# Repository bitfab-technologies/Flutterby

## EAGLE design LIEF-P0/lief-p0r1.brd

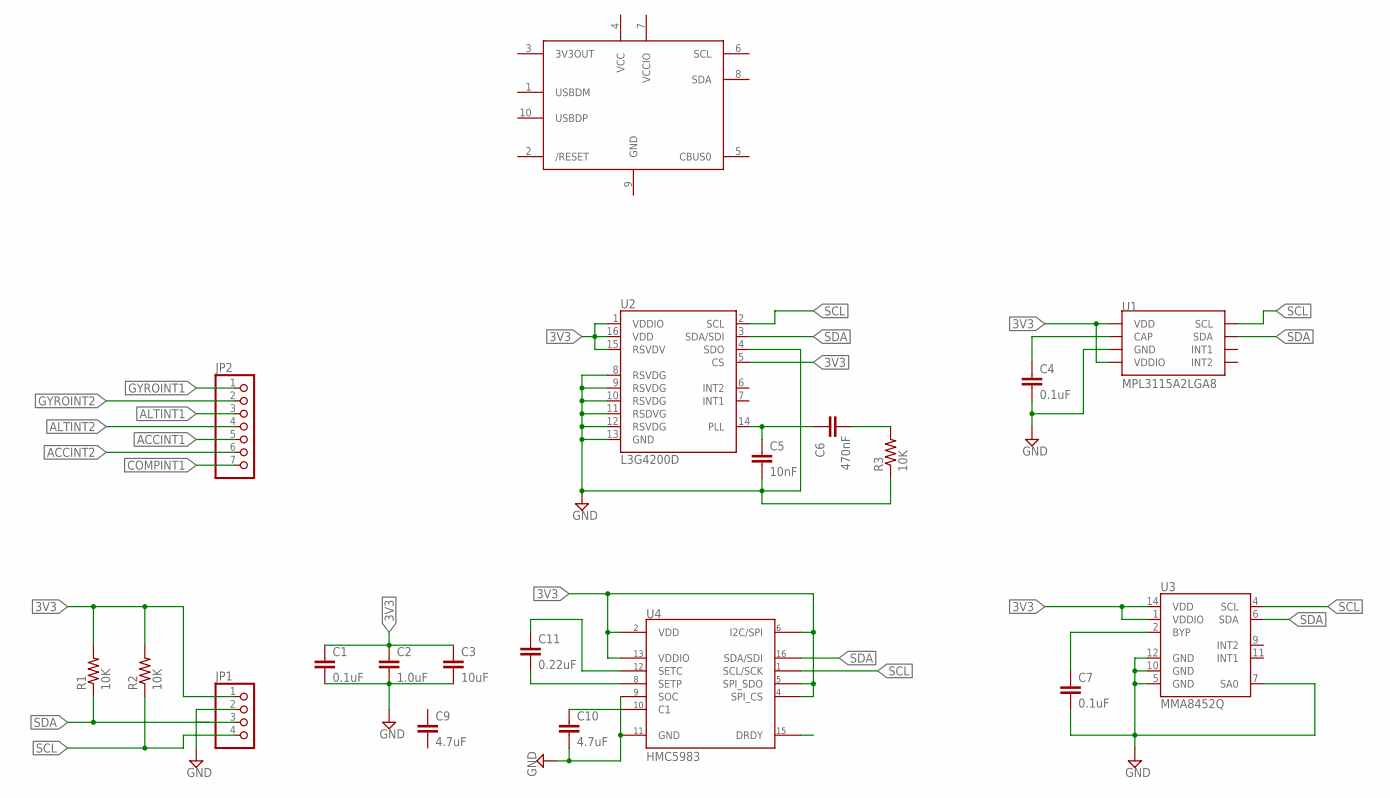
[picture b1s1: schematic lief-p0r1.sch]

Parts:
C1, C7: 0.1uF; 0603-CAP
C2: 1.0uF; 0805-CAP
C3: 10uF; 0805-CAP
C4: 0.1uF; 0805-CAP
C5: 10nF; 0805-CAP
C6: 470nF; 0805-CAP
C9: 4.7uF; 0603-CAP
C10: 4.7uF; 0805-CAP
C11: 0.22uF; 0805-CAP
JP1: PINHD-1X4; 1X04
JP2: PINHD-1X7; 1X07
R1, R2, R3: 10K; 0204V
U1: MPL3115A2LGA8; LGA8
U2: L3G4200D; LGA16-4X4
U3: MMA8452Q; QFN-16_0.5MM
U4: HMC5983; HMC5983-LPCC16
U$1: FT200XD; DFN-10

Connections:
3V3: C1.1, C2.1, C3.1, JP1.1, R1.2, R2.2, U1.1 (VDD), U1.4 (VDDIO), U2.1 (VDDIO), U2.5 (CS), U2.15 (RSVDV), U2.16 (VDD), U3.1 (VDDIO), U3.14 (VDD), U4.I2C/SPI, U4.SPI_CS/S1 (SPI_CS), U4.SPI_SDO, U4.VDD, U4.VDDIO
ACCINT1: JP2.5
ACCINT2: JP2.6
ALTINT1: JP2.3
ALTINT2: JP2.4
COMPINT1: JP2.7
GND: C1.2, C2.2, C3.2, C4.2, C5.2, C7.2, C10.2, JP1.2, JP1.3, R3.1, U1.3 (GND), U2.4 (SDO), U2.8 (RSVDG), U2.9 (RSVDG), U2.10 (RSVDG), U2.11 (RSDVG), U2.12 (RSVDG), U2.13 (GND), U3.5 (GND), U3.7 (SA0), U3.10 (GND), U3.12 (GND), U4.GND, U4.SOC
GYROINT1: JP2.1
GYROINT2: JP2.2
unnamed: C11.1, U4.SETC
unnamed: C4.1, U1.2 (CAP)
unnamed: C6.2, R3.2
unnamed: C5.1, C6.1, U2.14 (PLL)
unnamed: C7.1, U3.2 (BYP)
unnamed: C11.2, U4.SETP
unnamed: C10.1, U4.C1
SCL: JP1.4, R2.1, U1.8 (SCL), U2.2 (SCL), U3.4 (SCL), U4.SCL/SPI_SCK (SCL/SCK)
SDA: R1.1, U1.7 (SDA), U2.3 (SDA/SDI), U3.6 (SDA), U4.SDA/SPI_SDI (SDA/SDI)

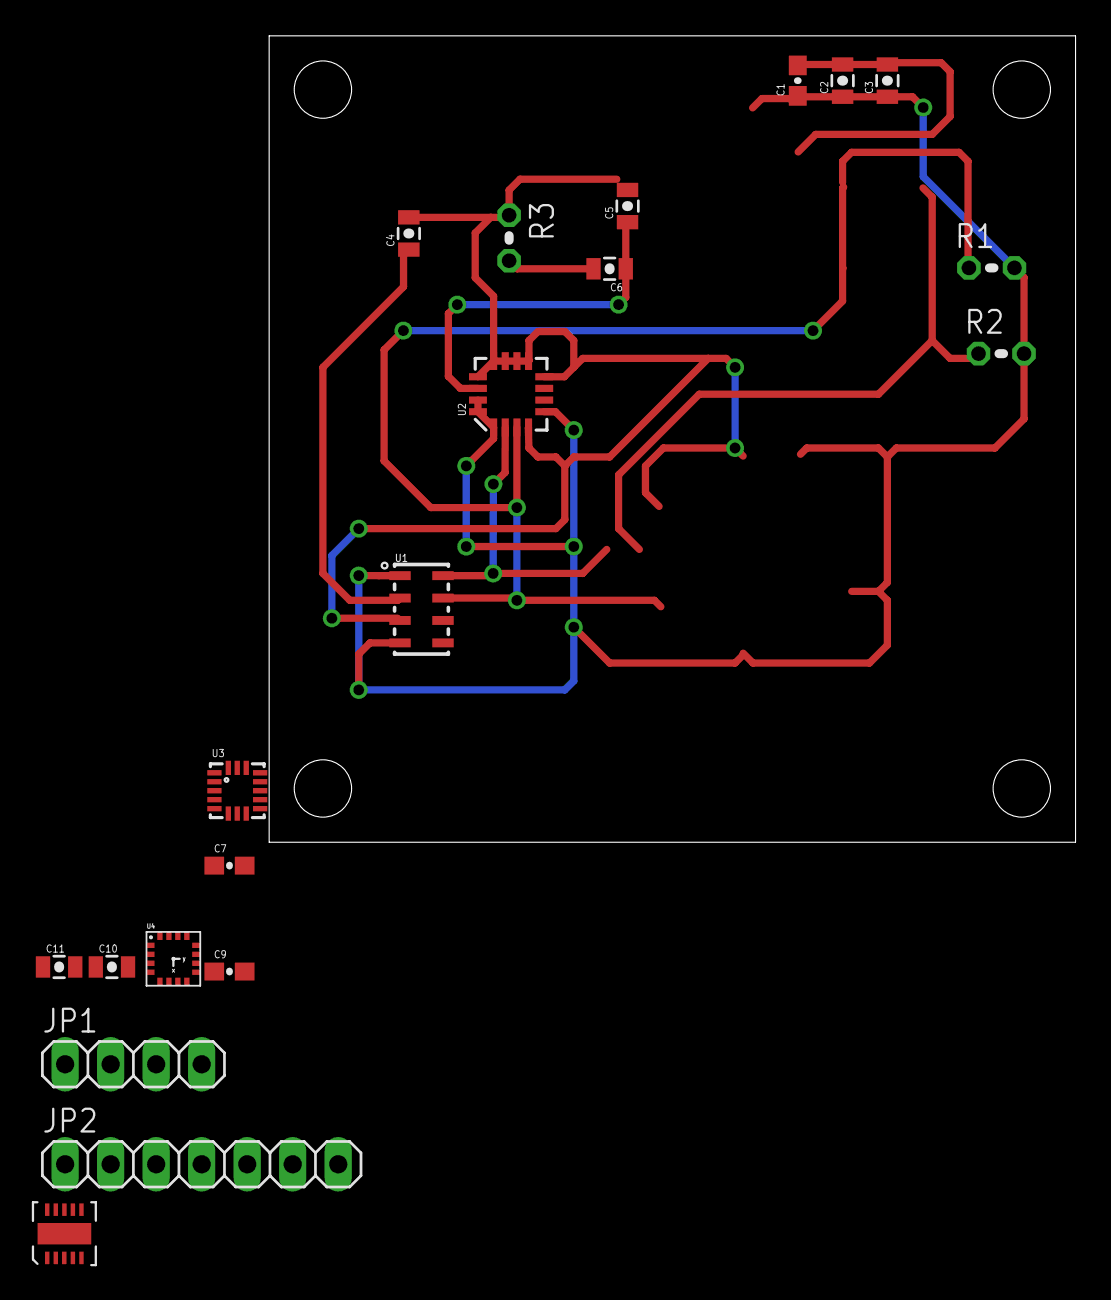
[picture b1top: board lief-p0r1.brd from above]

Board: 2 copper layers, 45.0 x 45.0 mm, 20 parts (0 on the bottom side), 11 nets.

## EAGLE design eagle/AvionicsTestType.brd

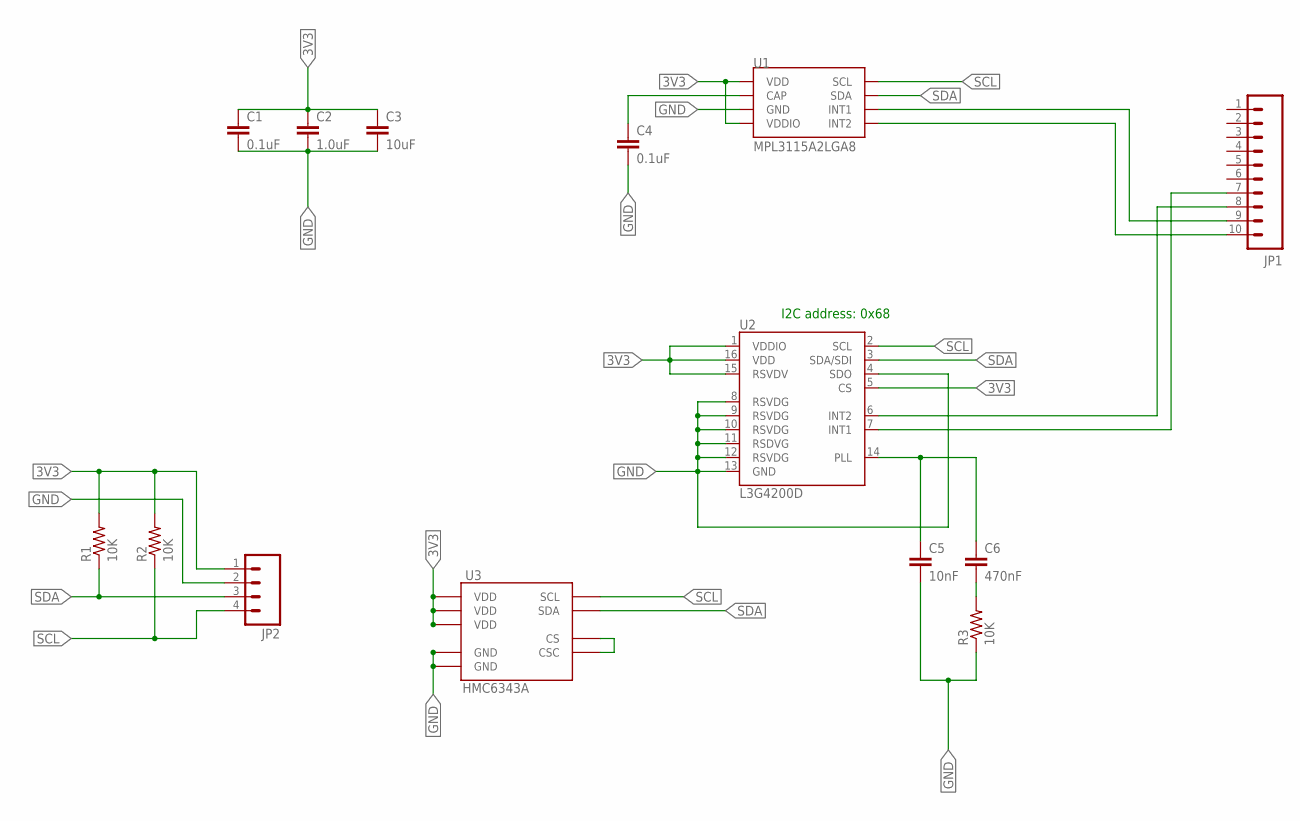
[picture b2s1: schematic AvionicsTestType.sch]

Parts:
C1: 0.1uF; 0603-CAP
C2: 1.0uF; 0805-CAP
C3: 10uF; 0805-CAP
C4: 0.1uF; 0805-CAP
C5: 10nF; 0805-CAP
C6: 470nF; 0805-CAP
JP1: M10LOCK; 1X10_LOCK
JP2: M04LOCK; 1X04_LOCK
R1, R2: 10K; M0805
R3: 10K; R0805
U1: MPL3115A2LGA8; LGA8
U2: L3G4200D; LGA16-4X4
U3: HMC6343A; LCC36

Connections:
3V3: C1.1, C2.1, C3.1, JP2.1, R1.2, R2.2, U1.1 (VDD), U1.4 (VDDIO), U2.1 (VDDIO), U2.5 (CS), U2.15 (RSVDV), U2.16 (VDD), U3.3 (VDD), U3.11 (VDD), U3.21 (VDD)
GND: C1.2, C2.2, C3.2, C4.2, C5.2, JP2.2, R3.1, U1.3 (GND), U2.4 (SDO), U2.8 (RSVDG), U2.9 (RSVDG), U2.10 (RSVDG), U2.11 (RSDVG), U2.12 (RSVDG), U2.13 (GND), U3.25 (GND), U3.29 (GND)
unnamed: JP1.10, U1.5 (INT2)
unnamed: U3.22 (CS), U3.35 (CSC)
unnamed: JP1.9, U1.6 (INT1)
unnamed: JP1.7, U2.7 (INT1)
unnamed: JP1.8, U2.6 (INT2)
unnamed: C4.1, U1.2 (CAP)
unnamed: C6.2, R3.2
unnamed: C5.1, C6.1, U2.14 (PLL)
SCL: JP2.4, R2.1, U1.8 (SCL), U2.2 (SCL), U3.32 (SCL)
SDA: JP2.3, R1.1, U1.7 (SDA), U2.3 (SDA/SDI), U3.36 (SDA)

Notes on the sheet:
I2C address: 0x68

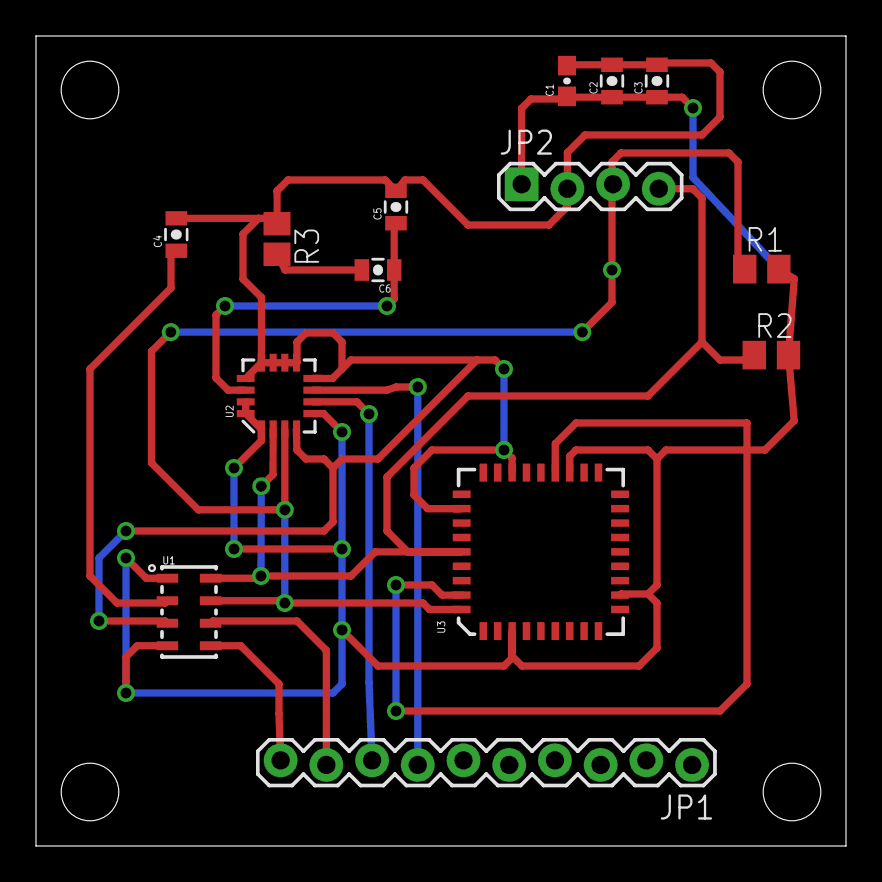
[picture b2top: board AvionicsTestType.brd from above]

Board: 2 copper layers, 45.0 x 45.0 mm, 14 parts (0 on the bottom side), 12 nets.

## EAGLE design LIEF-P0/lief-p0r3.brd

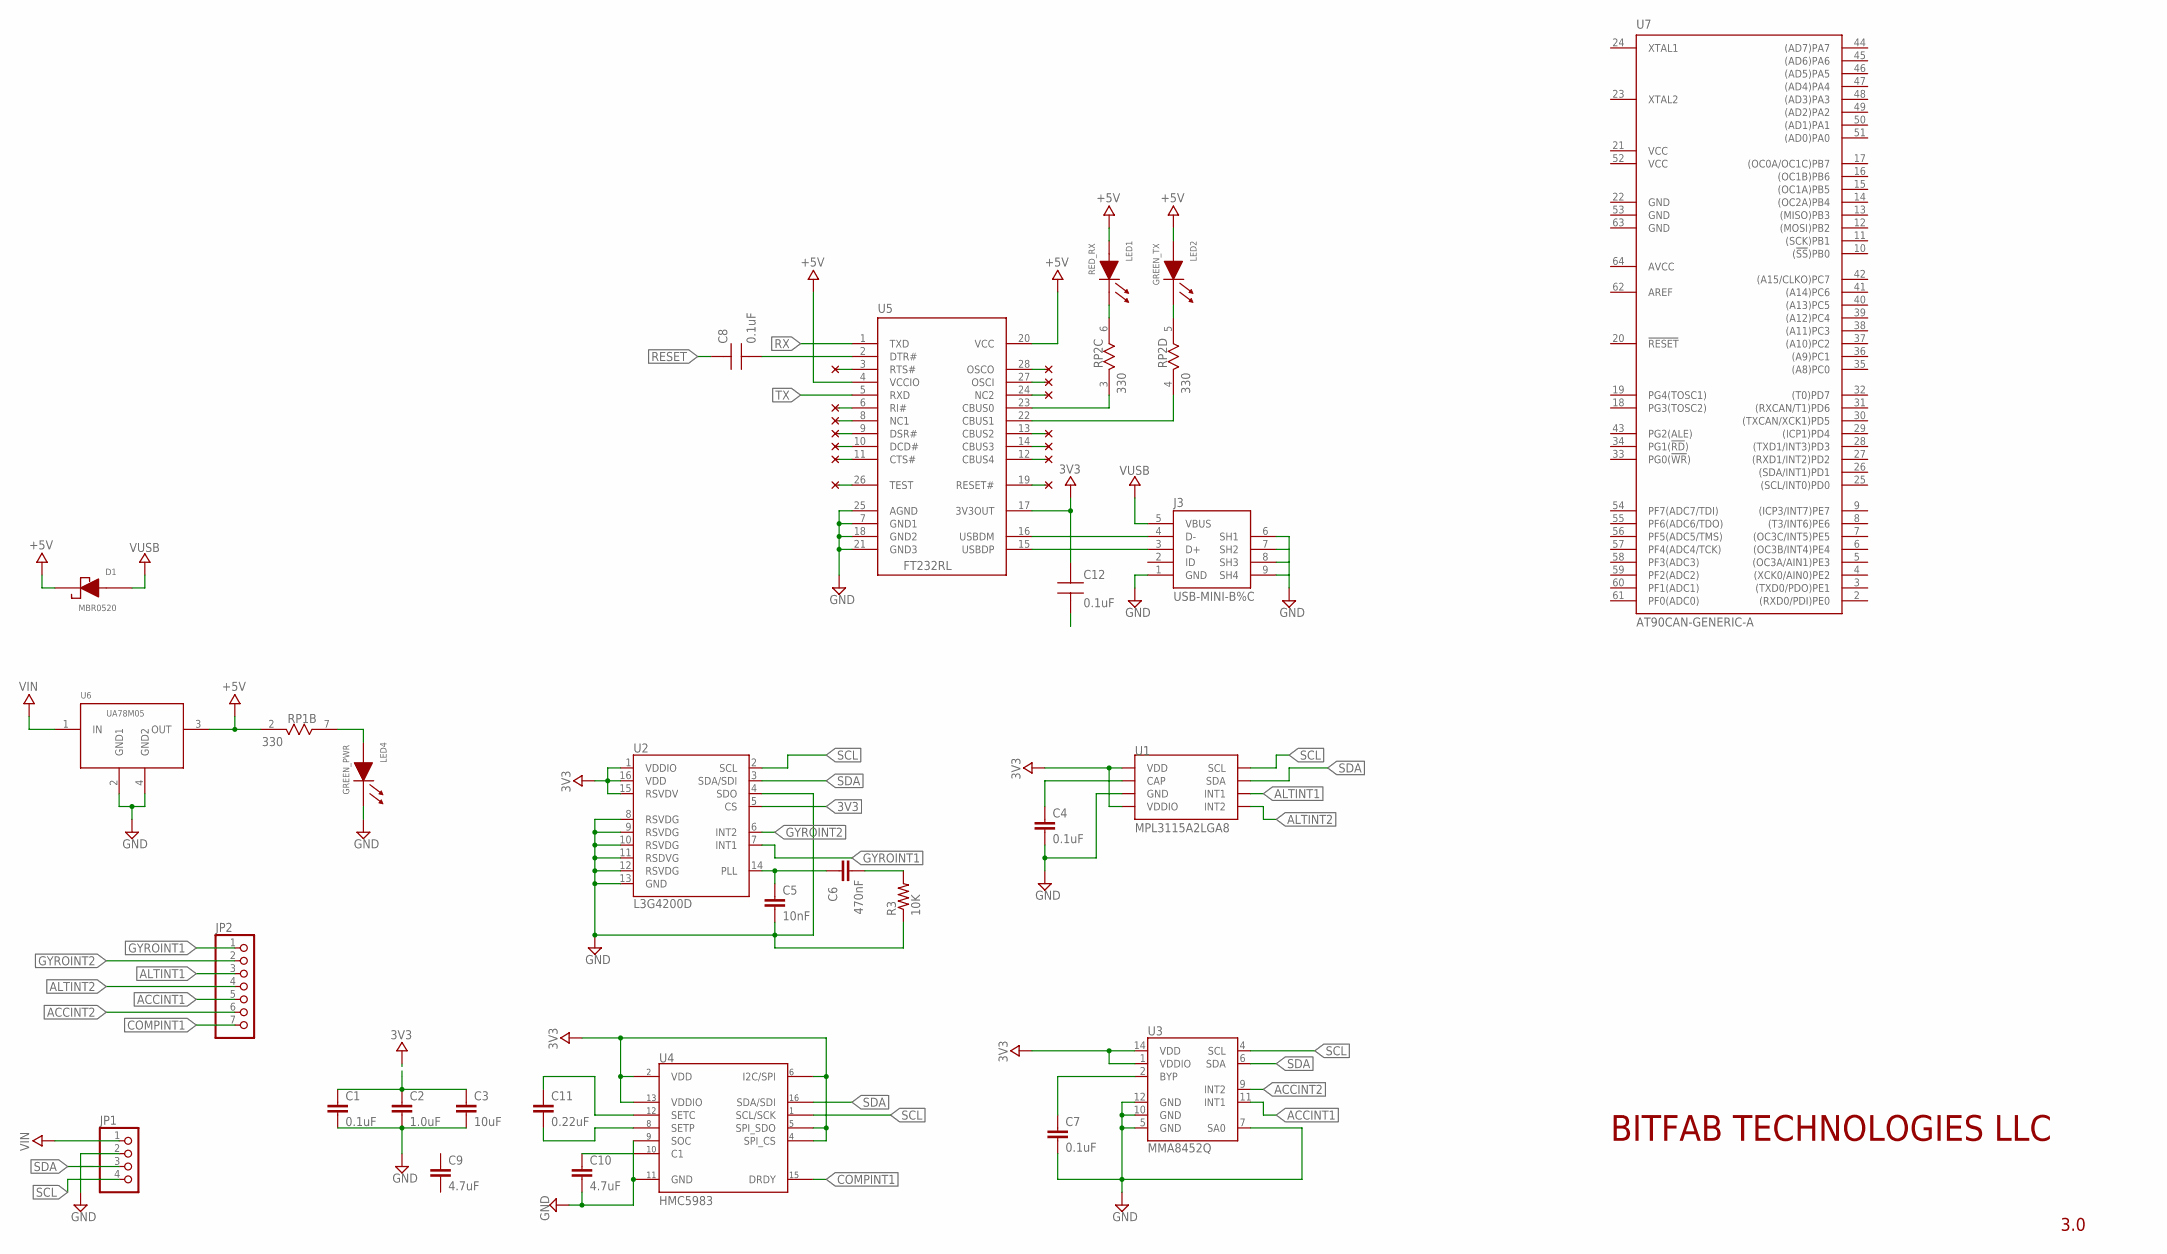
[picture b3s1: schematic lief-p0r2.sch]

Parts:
C1, C7: 0.1uF; 0603-CAP
C2: 1.0uF; 0805-CAP
C3: 10uF; 0805-CAP
C4: 0.1uF; 0805-CAP
C5: 10nF; 0805-CAP
C6: 470nF; 0805-CAP
C8, C12: 0.1uF; CAP0805-NP
C9: 4.7uF; 0603-CAP
C10: 4.7uF; 0805-CAP
C11: 0.22uF; 0805-CAP
D1: MBR0520; SOD-123
J3: USB-MINI-B%C; USB-MINI-B_2
JP1: PINHD-1X4; 1X04
JP2: PINHD-1X7; 1X07
LED1: RED_RX; LED0805
LED2: GREEN_TX; LED0805
LED4: GREEN_PWR; LED0805
R3: 10K; 0204V
RP1, RP2: 330; RES4NT
U1: MPL3115A2LGA8; LGA8
U2: L3G4200D; LGA16-4X4
U3: MMA8452Q; QFN-16_0.5MM
U4: HMC5983; HMC5983-LPCC16
U5: FT232RL; SSOP28
U6: UA78M05; SOT223
U7: AT90CAN-GENERIC-A; TQFP64

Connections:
3V3: C1.1, C2.1, C3.1, C12.1, U1.1 (VDD), U1.4 (VDDIO), U2.1 (VDDIO), U2.5 (CS), U2.15 (RSVDV), U2.16 (VDD), U3.1 (VDDIO), U3.14 (VDD), U4.I2C/SPI, U4.SPI_CS/S1 (SPI_CS), U4.SPI_SDO, U4.VDD, U4.VDDIO, U5.17 (3V3OUT)
+5V: D1.1 (CA), LED1.2 (AN), LED2.2 (AN), RP1.2 (1), U5.4 (VCCIO), U5.20 (VCC), U6.3 (OUT)
ACCINT1: JP2.5, U3.11 (INT1)
ACCINT2: JP2.6, U3.9 (INT2)
ALTINT1: JP2.3, U1.6 (INT1)
ALTINT2: JP2.4, U1.5 (INT2)
AVCC: U7.64 (AVCC)
COM: C12.2
COMPINT1: JP2.7, U4.DRDY
GND: C1.2, C2.2, C3.2, C4.2, C5.2, C7.2, C10.2, J3.1 (GND), J3.6 (SH1), J3.7 (SH2), J3.8 (SH3), J3.9 (SH4), JP1.2, JP1.3, LED4.1 (CA), R3.1, U1.3 (GND), U2.4 (SDO), U2.8 (RSVDG), U2.9 (RSVDG), U2.10 (RSVDG), U2.11 (RSDVG), U2.12 (RSVDG), U2.13 (GND), U3.5 (GND), U3.7 (SA0), U3.10 (GND), U3.12 (GND), U4.GND, U4.SOC, U5.7 (GND1), U5.18 (GND2), U5.21 (GND3), U5.25 (AGND), U6.2 (GND1), U6.4 (GND2), U7.22 (GND), U7.53 (GND), U7.63 (GND)
GYROINT1: JP2.1, U2.7 (INT1)
GYROINT2: JP2.2, U2.6 (INT2)
unnamed: LED4.2 (AN), RP1.7 (2)
unnamed: J3.3 (D+), U5.15 (USBDP)
unnamed: J3.4 (D-), U5.16 (USBDM)
unnamed: C8.2, U5.2 (DTR#)
unnamed: C11.1, U4.SETC
unnamed: C4.1, U1.2 (CAP)
unnamed: C6.2, R3.2
unnamed: C5.1, C6.1, U2.14 (PLL)
unnamed: C7.1, U3.2 (BYP)
unnamed: C11.2, U4.SETP
unnamed: RP2.3 (1), U5.23 (CBUS0)
unnamed: C10.1, U4.C1
unnamed: RP2.4 (1), U5.22 (CBUS1)
unnamed: LED1.1 (CA), RP2.6 (2)
unnamed: LED2.1 (CA), RP2.5 (2)
RESET: C8.1
RX: U5.1 (TXD)
SCL: JP1.4, U1.8 (SCL), U2.2 (SCL), U3.4 (SCL), U4.SCL/SPI_SCK (SCL/SCK)
SDA: U1.7 (SDA), U2.3 (SDA/SDI), U3.6 (SDA), U4.SDA/SPI_SDI (SDA/SDI)
TX: U5.5 (RXD)
VCC: U7.21 (VCC), U7.52 (VCC)
VIN: JP1.1, U6.1 (IN)
VUSB: D1.2 (AN), J3.5 (VBUS)

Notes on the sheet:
3.0
BITFAB TECHNOLOGIES LLC

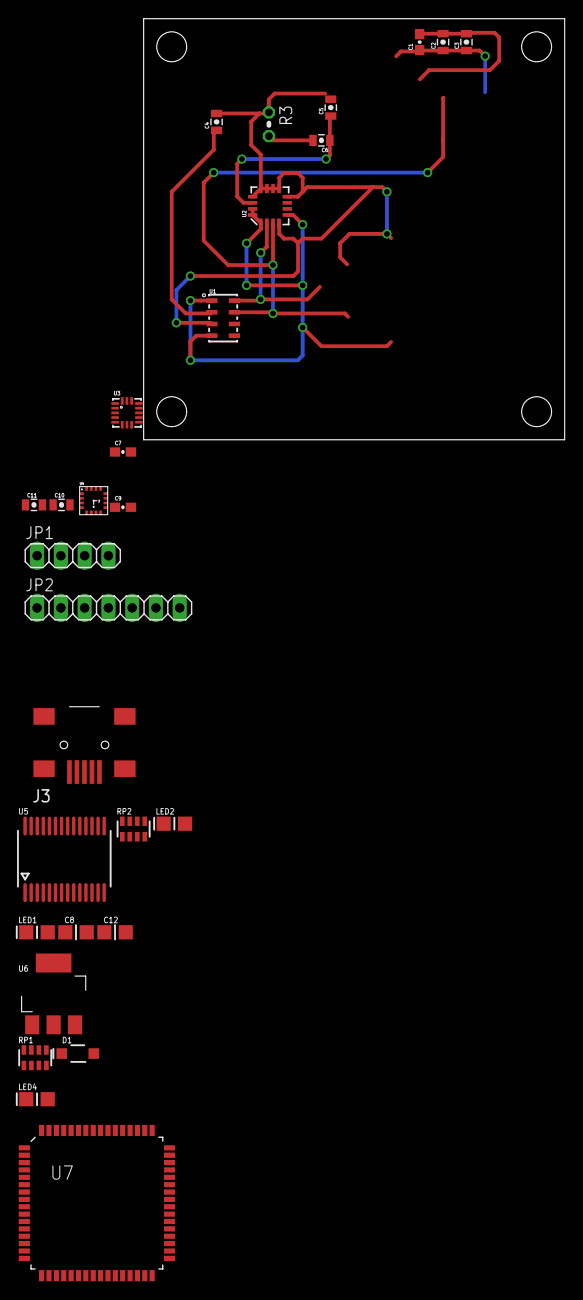
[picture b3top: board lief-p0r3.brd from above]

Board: 2 copper layers, 45.0 x 45.0 mm, 29 parts (0 on the bottom side), 30 nets.

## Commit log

2015-10-23 Initial Commit.
2016-03-24 Revision 3 of the LIEF hardware design.

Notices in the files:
parts and their libraries:
SparkFun-Sensors: Licensing: Creative Commons ShareAlike 4.0 International - https://creativecommons.org/licenses/by-sa/4.0
bitfab: BitFab Technologies, LLC. All rights reserved.
